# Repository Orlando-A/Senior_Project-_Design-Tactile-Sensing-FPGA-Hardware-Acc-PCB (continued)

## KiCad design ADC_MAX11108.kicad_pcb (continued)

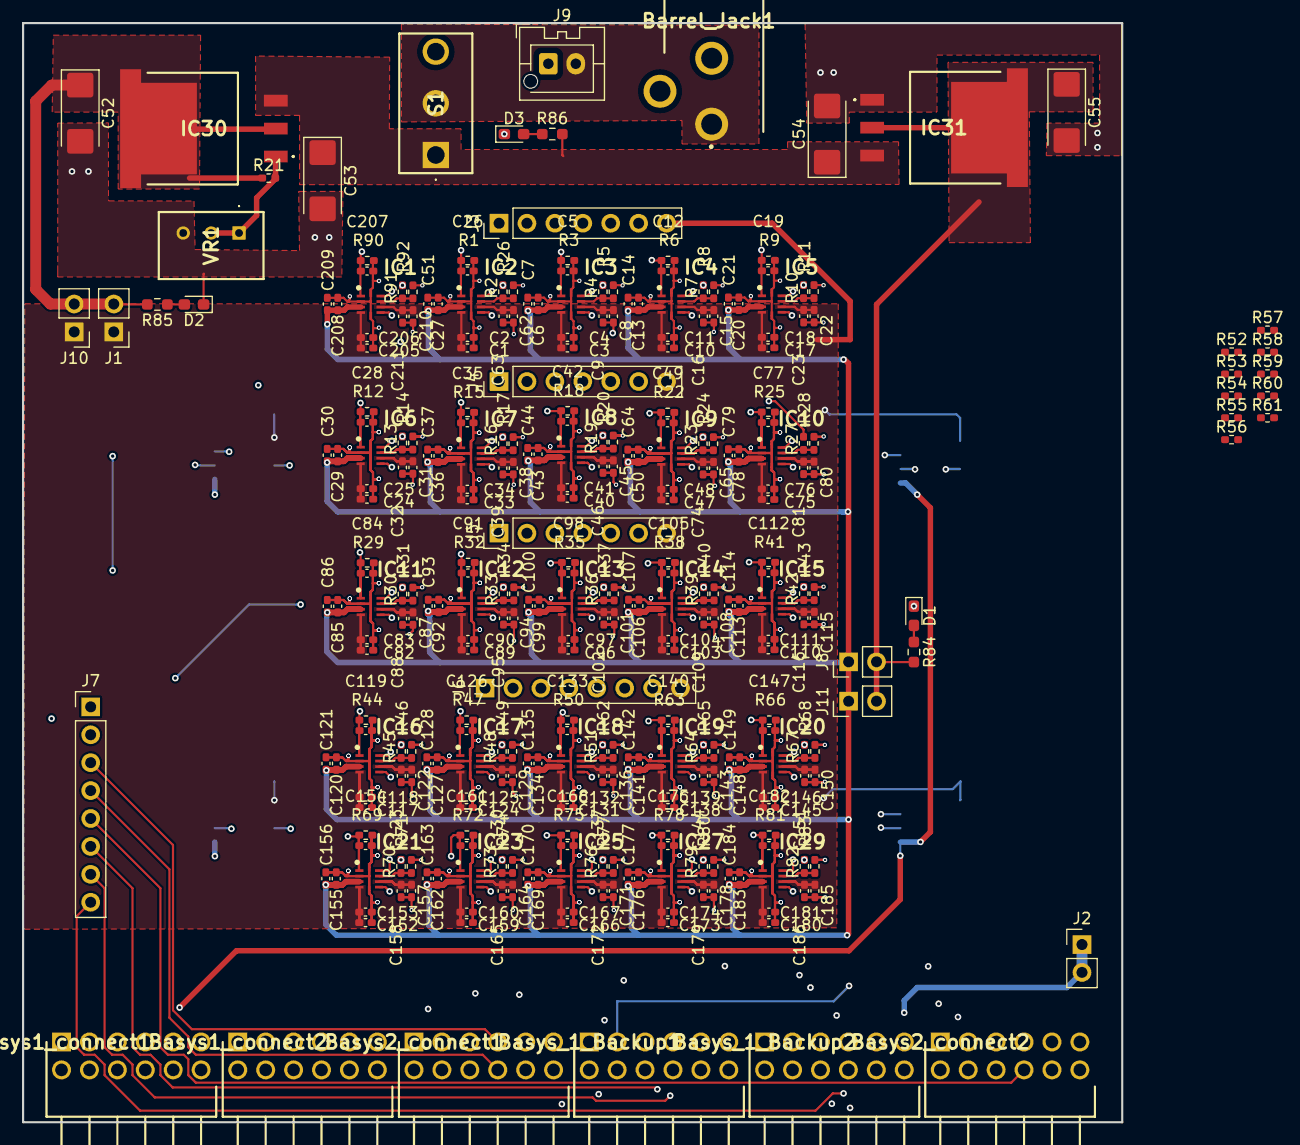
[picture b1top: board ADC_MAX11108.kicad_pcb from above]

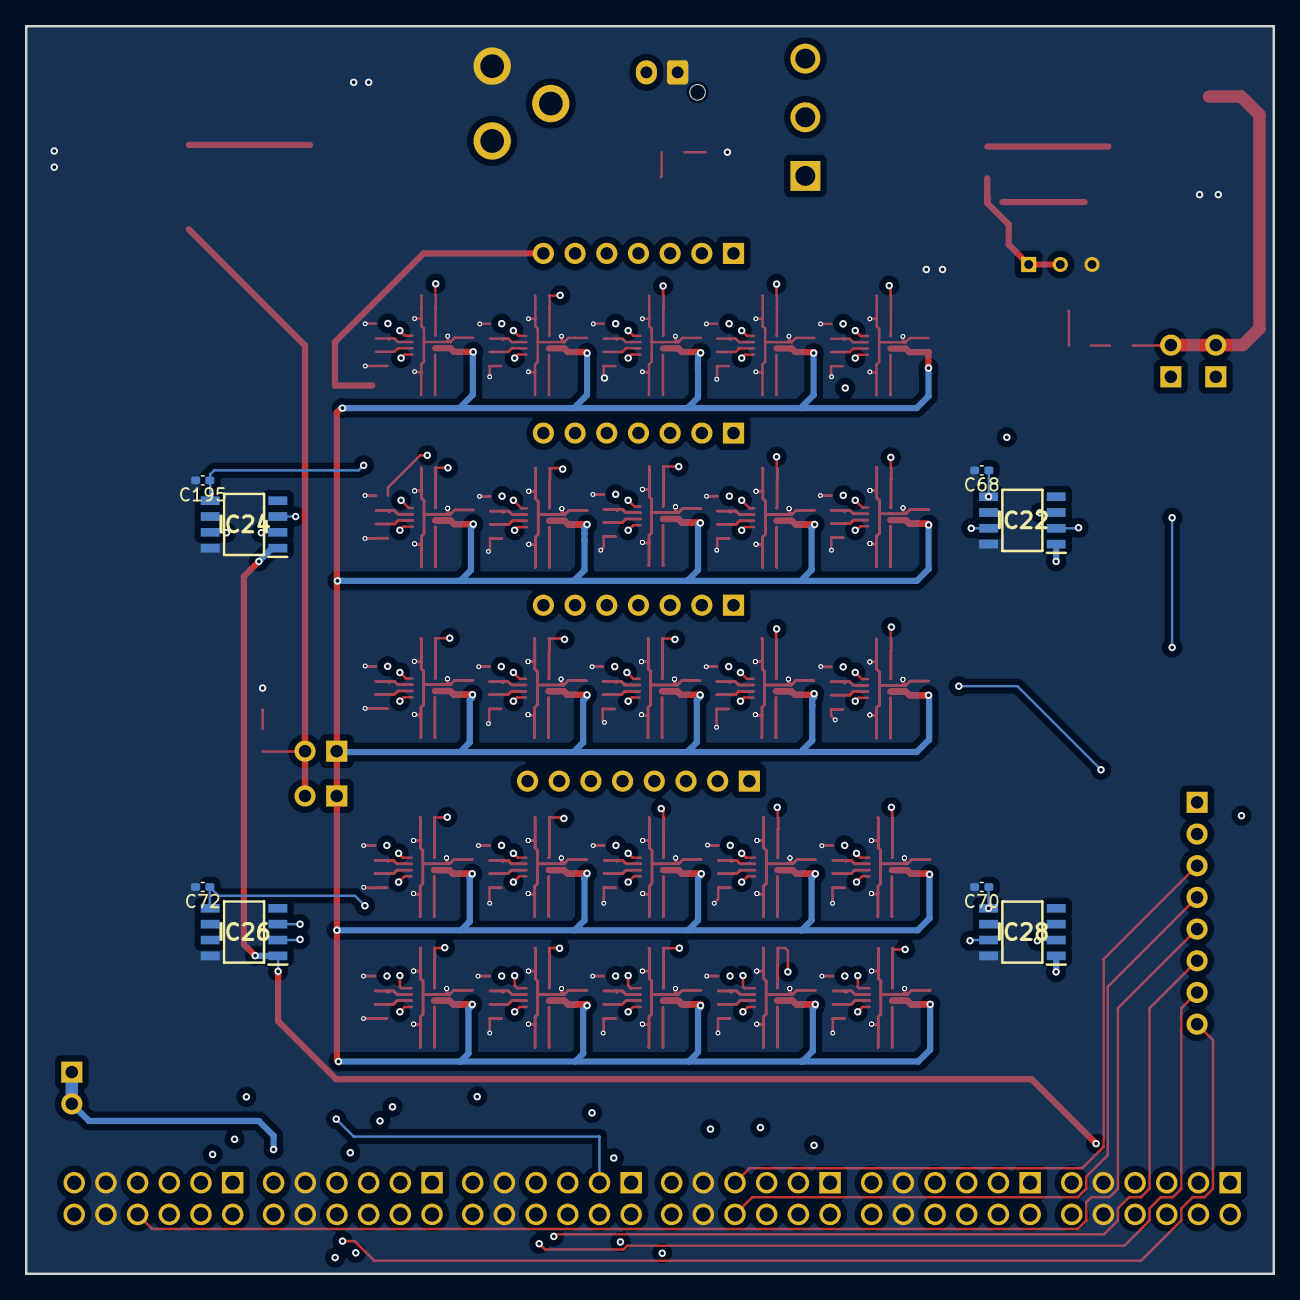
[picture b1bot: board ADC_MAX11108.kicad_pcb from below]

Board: 4 copper layers, 100.0 x 100.0 mm, 326 parts (8 on the bottom side), 107 nets.

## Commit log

2026-03-04 Initial commit of project
2026-03-05 completed duplicating the ADCs in the schematic
2026-03-05 figured out footprint issue and replicated the 25 ADCs in the routing part as well
2026-03-19 Updated schematic and PCB layout, no more precision Vrefs
2026-03-19 arranged the rest of the parts onto the board
2026-03-21 Finished Power section routing, added LED indicators
2026-03-21 Routed most of the Douts, and all of the CS & SCLK
2026-03-21 added GND Vias
2026-03-23 added routing for the connectors
2026-03-23 fixed Vadj plane, cleaned up connections
